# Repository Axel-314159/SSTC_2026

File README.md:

# SSTC 2026

Hardware source files for my 2026 Solid State Tesla Coil design.

## Concept

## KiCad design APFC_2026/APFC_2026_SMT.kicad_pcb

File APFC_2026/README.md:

# Active Power Factor Correction (APFC) board

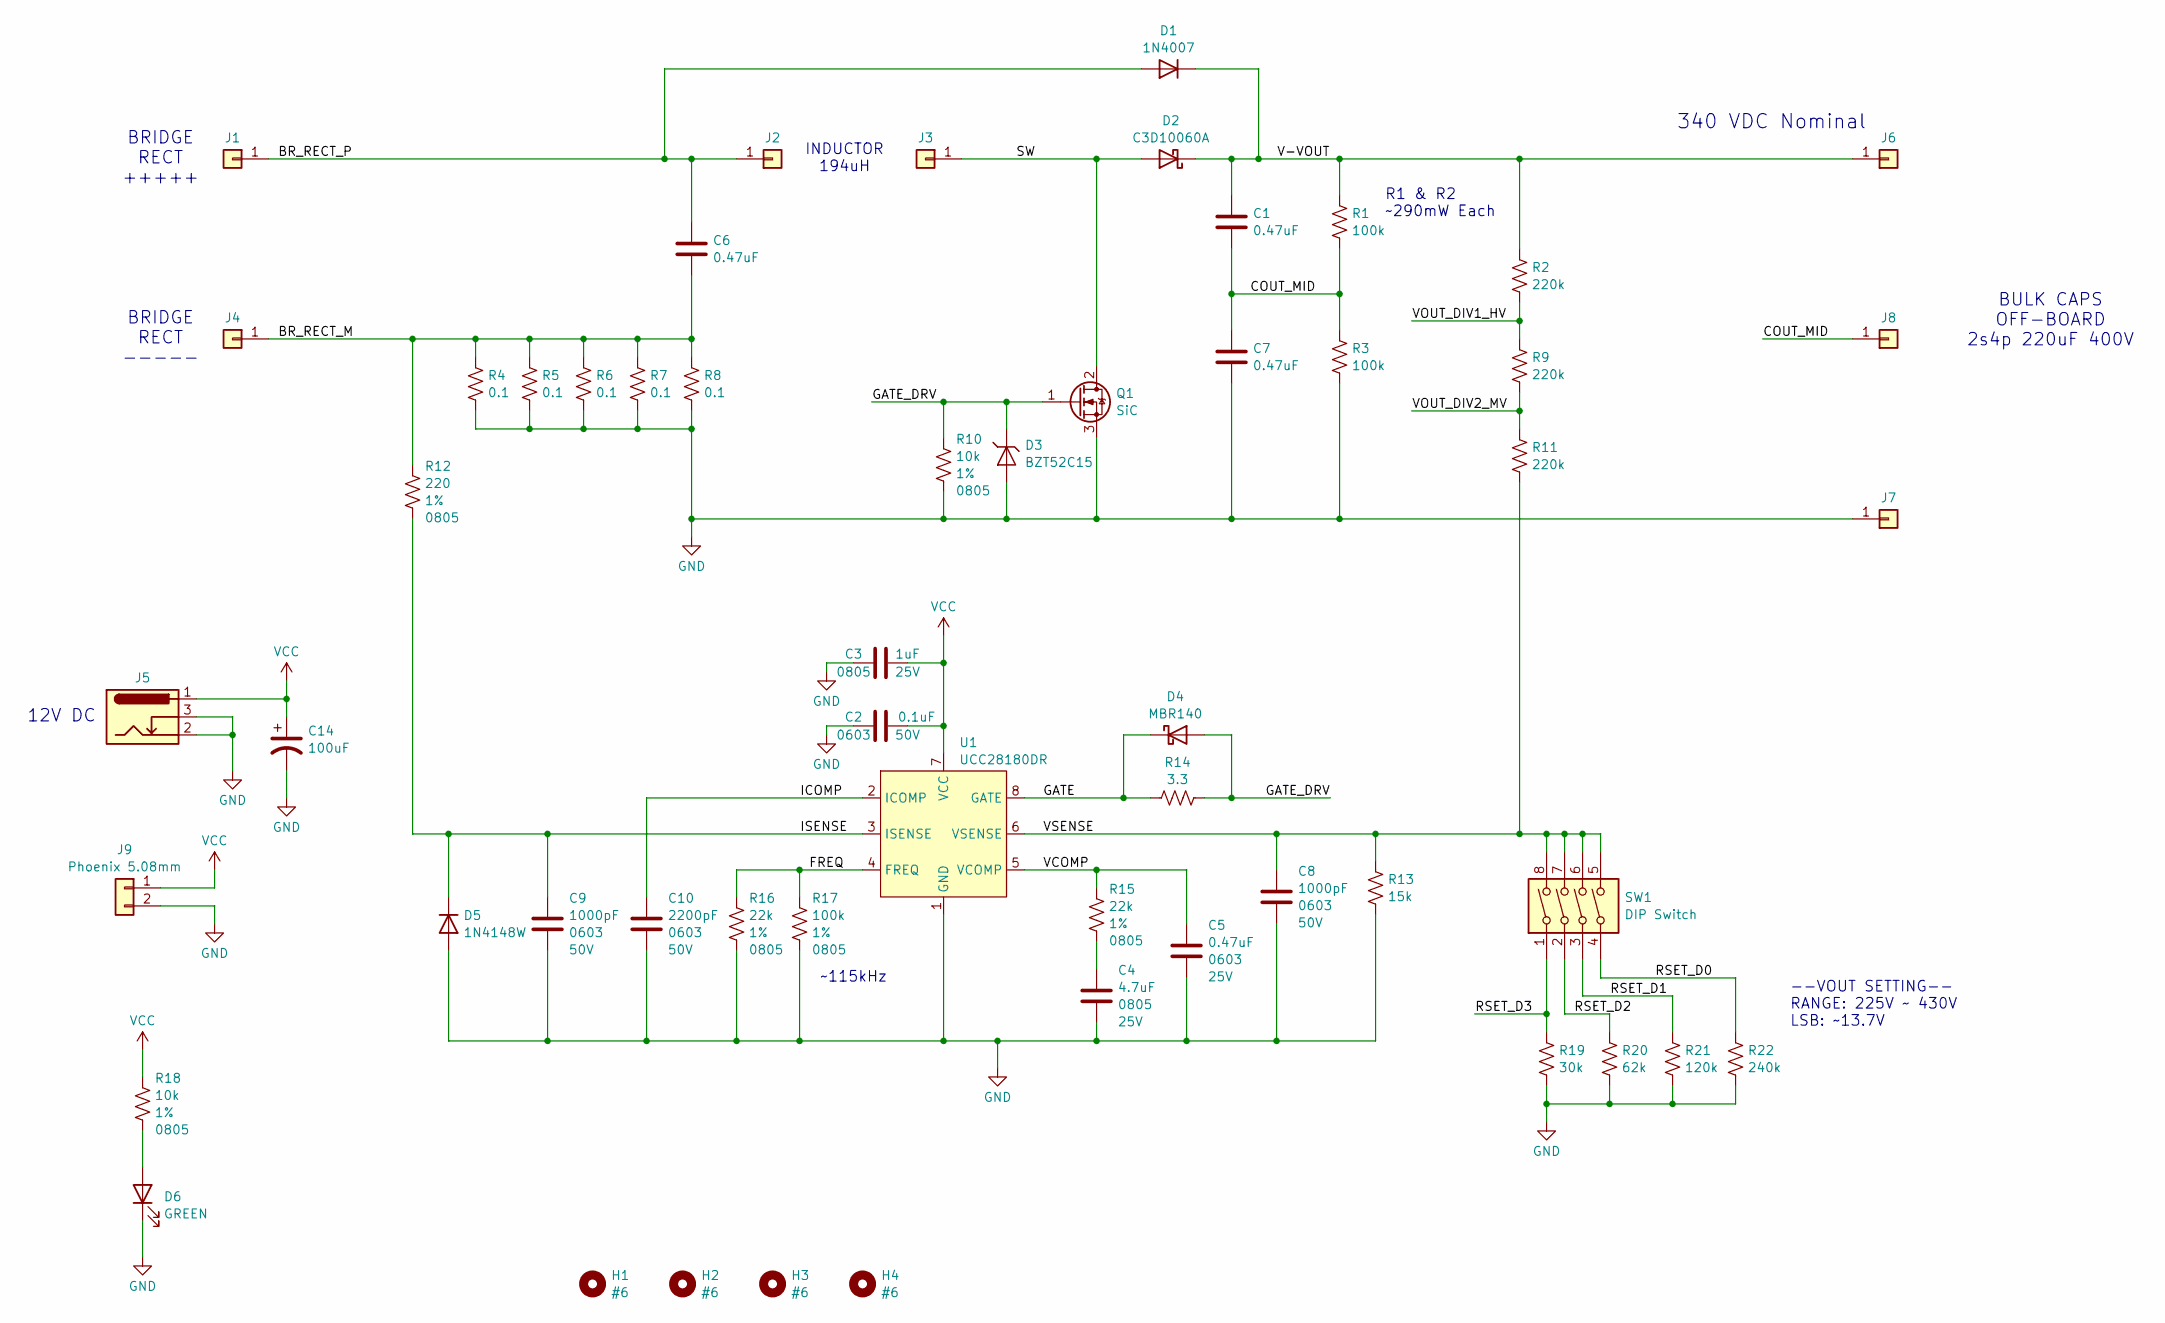
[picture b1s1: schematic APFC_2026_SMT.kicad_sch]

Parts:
C1, C6, C7: 0.47uF; C_Rect_L18.0mm_W8.0mm_P15.00mm_FKS3_FKP3
C2: 0.1uF; C_0603_1608Metric; Tolerance 5%; Voltage Rating 50V; Mfr Part # CL10B104JB8NNNC; JLCPCB_PN C24452
C3: 1uF; C_0805_2012Metric; Tolerance 10%; Voltage Rating 25V; Mfr Part # CL21B105KAFNNNE; JLCPCB_PN C116352
C4: 4.7uF; C_0805_2012Metric; Tolerance 10%; Voltage Rating 25V; Mfr Part # CL21B475KAFNNNE; JLCPCB_PN C98195
C5: 0.47uF; C_0603_1608Metric; Tolerance 10%; Voltage Rating 25V; Mfr Part # CL10B474KA8NNNC; JLCPCB_PN C1623
C8, C9: 1000pF; C_0603_1608Metric; Tolerance 10%; Voltage Rating 50V; Mfr Part # CL10B102KB8NNNC; JLCPCB_PN C1588
C10: 2200pF; C_0603_1608Metric; Tolerance 5%; Voltage Rating 50V; Mfr Part # CL10C222JB8NNNC; JLCPCB_PN C33353
C14: 100uF; CP_Radial_D10.0mm_P5.00mm
D1: 1N4007; D_DO-41_SOD81_P10.16mm_Horizontal
D2: C3D10060A; TO-220-2_Vertical
D3: BZT52C15; D_SOD-123; MFG_PN BZT52C15; JLCPCB Part # C173427
D4: MBR140; D_SOD-123F; MFG_PN MBR130T3G
D5: 1N4148W; D_SOD-123; MFG_PN 1N4148W; JLCPCB Part # C176288
D6: GREEN; LED_D3.0mm
H1, H2, H3, H4: #6; MountingHole_3.7mm
J1, J2, J3, J4, J6, J7: Conn_01x01; SolderWire-1.5sqmm_1x01_D1.7mm_OD3.9mm
J5: Barrel_Jack_Switch; BarrelJack_Wuerth_6941xx301002
J8: Conn_01x01; SolderWire-0.75sqmm_1x01_D1.25mm_OD2.3mm
J9: Phoenix 5.08mm; PhoenixContact_MSTBA_2,5_2-G-5,08_1x02_P5.08mm_Horizontal
Q1: SiC; TO-247-3_Vertical
R1, R3: 100k; R_Axial_DIN0309_L9.0mm_D3.2mm_P12.70mm_Horizontal
R2, R9, R11: 220k; R_1206_3216Metric_Pad1.30x1.75mm_HandSolder
R4, R5, R6, R7, R8: 0.1; R_Axial_DIN0411_L9.9mm_D3.6mm_P12.70mm_Horizontal
R10, R18: 10k; R_0805_2012Metric; Tolerance 1%; Mfr Part # RC0805FR-0710KL; JLCPCB_PN C84376
R12: 220; R_0805_2012Metric; Tolerance 1%; Mfr Part # RC0805FR-07220RL; JLCPCB_PN C114519
R13: 15k; R_0805_2012Metric_Pad1.20x1.40mm_HandSolder
R14: 3.3; R_0805_2012Metric_Pad1.20x1.40mm_HandSolder
R15, R16: 22k; R_0805_2012Metric; Tolerance 1%; Mfr Part # RC0805FR-0722KL; JLCPCB_PN C114565
R17: 100k; R_0805_2012Metric; Tolerance 1%; Mfr Part # RC0805FR-07100KL; JLCPCB_PN C96346
R19: 30k; R_0805_2012Metric_Pad1.20x1.40mm_HandSolder
R20: 62k; R_0805_2012Metric_Pad1.20x1.40mm_HandSolder
R21: 120k; R_0805_2012Metric_Pad1.20x1.40mm_HandSolder
R22: 240k; R_0805_2012Metric_Pad1.20x1.40mm_HandSolder
SW1: DIP Switch; DIP-8_W7.62mm_Socket
U1: UCC28180DR; SOIC-8_3.9x4.9mm_P1.27mm; MFG_PN UCC28180DR; JLCPCB Part # C88567

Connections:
/BR_RECT_M: C6.2, J4.1, R4.1, R5.1, R6.1, R7.1, R8.1, R12.1
/BR_RECT_P: C6.1, D1.2 (A), J1.1, J2.1
/COUT_MID: C1.2, C7.1, J8.1, R1.2, R3.1
/FREQ: R16.1, R17.1, U1.4 (FREQ)
/GATE: D4.1 (K), R14.1, U1.8 (GATE)
/GATE_DRV: D3.1 (K), D4.2 (A), Q1.1 (G), R10.1, R14.2
/ICOMP: C10.1, U1.2 (ICOMP)
/ISENSE: C9.1, D5.1 (K), R12.2, U1.3 (ISENSE)
/RSET_D0: R22.2, SW1.4
/RSET_D1: R21.2, SW1.3
/RSET_D2: R20.2, SW1.2
/RSET_D3: R19.2, SW1.1
/SW: D2.2 (A), J3.1, Q1.2 (D)
/V-VOUT: C1.1, D1.1 (K), D2.1 (K), J6.1, R1.1, R2.2
/VCOMP: C5.1, R15.1, U1.5 (VCOMP)
/VOUT_DIV1_HV: R2.1, R9.2
/VOUT_DIV2_MV: R9.1, R11.2
/VSENSE: C8.1, R11.1, R13.2, SW1.5, SW1.6, SW1.7, SW1.8, U1.6 (VSENSE)
GND: C2.1, C3.1, C4.2, C5.2, C7.2, C8.2, C9.2, C10.2, C14.2, D3.2 (A), D5.2 (A), D6.1 (K), J5.2, J5.3, J7.1, J9.2, Q1.3 (S), R3.2, R4.2, R5.2, R6.2, R7.2, R8.2, R10.2, R13.1, R16.2, R17.2, R19.1, R20.1, R21.1, R22.1, U1.1 (GND)
unnamed: C4.1, R15.2
unnamed: D6.2 (A), R18.2
VCC: C2.2, C3.2, C14.1, J5.1, J9.1, R18.1, U1.7 (VCC)

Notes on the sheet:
12V DC
R1 & R2 ~290mW Each
BRIDGE RECT +++++
BULK CAPS OFF-BOARD 2s4p 220uF 400V
~115kHz
--VOUT SETTING-- RANGE: 225V ~ 430V LSB: ~13.7V
340 VDC Nominal
BRIDGE RECT -----
INDUCTOR 194uH

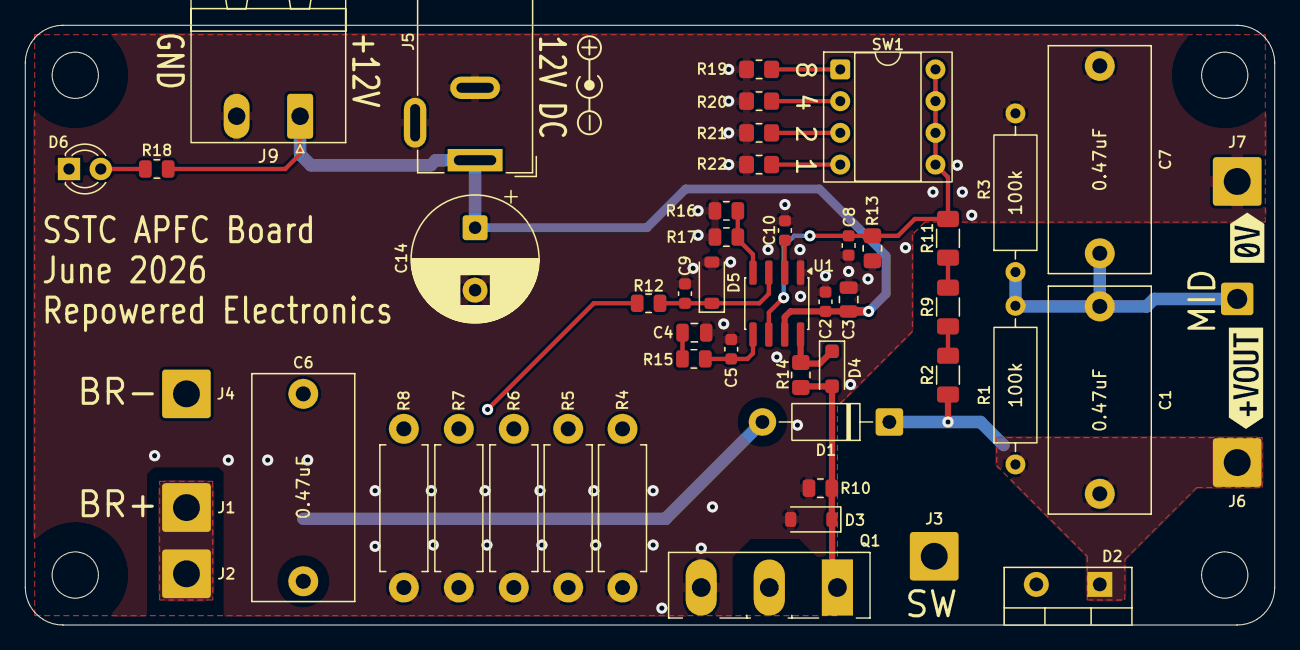
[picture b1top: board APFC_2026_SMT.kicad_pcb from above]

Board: 2 copper layers, 100.0 x 48.0 mm, 57 parts (0 on the bottom side), 22 nets.

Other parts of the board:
kibuzzard-6A3E27F1: G***; kibuzzard-6A3E27F1
kibuzzard-6A3624E5: G***; kibuzzard-6A3624E5
